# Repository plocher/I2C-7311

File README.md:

# I2C-7311
## License: CERN Open Hardware Licence v1.2

IO Expander with 4x IO4 connections

### Introduction

This board was originally produced to help me build control panels for
my model railroad - I needed to connect many different buttons, switches
and lights to an Arduino, and also connect the Arduino to a
communications bus (Ethernet, CAN or Loconet), and I couldn\'t find
anything that had both high IO point density AND visual feedback.

I started with a simple I2C based 32-pin Arduino
[IOShield](/pages/IOShield "wikilink") with monitoring LEDs on each pin
(Active-LOW inputs, LED is on when pin is grounded, writing a \"1\" to
the port pulls it to ground). I was aiming to support up to the max I2C
devices that can be used together, with the 8-bit board
[I2C-8574-IO](/pages/I2C-8574-IO "wikilink") (deprecated), that was a total of
8x boards with 128 i/o points.

The 7311 IO expanders used here will support up to 64 boards, with 1024
potential I/O points.

This latest design moves from overly generic and/or overly specialized
designs to a generic design with daughterboards that encapsulate the
appliance-specific buffering and logic. The benefits provided by these
IOB boards include:

-   Improved I/O bank utilization (leftover capacity is now a multiple
    of 4-bit daughtercard instead of 16-bit I2C card\...)
-   Riser height eliminates having to custom cut 3M track
-   Allows deprecation of cabling intensive signal driver IO4 and I2C
    boards
-   Allows custom circuitry to be added to Signal, Detector and Turtle
    drivers

### Cautions

With several hundred IO loads, and up to 256 external breakout devices,
a suitable power supply (or supplies) must be used.

In practice, a 3A 9-12VDC supply a good choice for most small to medium
sized control points.

This supply needs to power the core processor, its direct IO loads, the
I2C expander chain AND provide \~100mA to each IO4 device. Instead of
relying on the Arduino\'s onboard regulated supply (which is only good
for about 100mA itself), each board has its own regulator with a common
supply feed that can handle up to 4A @ 12v. If more power is needed, the
daisy chained power feed thru can be replaced with a per-board
independent supply.

### Specifications

This IO board is based on the MAX7311/12 16 bit IO Expander, with a a
bank of 4x I/O Boards. These IOBs contain buffered LED drivers connected
to LEDs that show the status of the I/O lines in real time. They also
contain the needed circuitry to drive / sense the appliances connected
to them. See

-   [IOB-Inputs](/pages/IOB-Inputs "wikilink") 4x buffered inputs
-   [IOB-Outputs](/pages/IOB-Outputs "wikilink") 4x buffered outputs
-   [IOB-Turtle](/pages/IOB-Turtle "wikilink") 1x buffered output and 3x buffered inputs
-   [IOB-Signal](/pages/IOB-Signal "wikilink") 2x RGB signal head driver (Dark, Stop, Approach, Clear)

Each board provides a latched set of 16x IO points, with each point
being software selectable to be either an input or an output. The
individual points are reasonably protected from the environment, and can
sink 10 mA each (with the MAX7312, they can also drive \~20mA). By using
active low inputs and outputs, the effects of environmental noise are
reduced - remote sensors only need to ground an I/O point to register
activity.

#### Communication Protocol {#communication_protocol}

```C++
Simple I2C 16-bit Reads and Writes:
uint16_t I2Cexpander::read7311() {
    uint16_t data = 0;
    Wire.beginTransmission(_i2c_address);
    Wire.write(REGISTER_7311INPUT);
    Wire.endTransmission();
    // Wire.beginTransmission(_i2c_address);
    Wire.requestFrom(_i2c_address, (uint8_t)2);
    if(Wire.available()) {
        data = Wire.read();
    }
    if(Wire.available()) {
        data |= (Wire.read() << 8);
    }
    // Wire.endTransmission();
    return data;
}

void I2Cexpander::write7311(uint16_t data) {
    data = data | _config;
    Wire.beginTransmission(_i2c_address);
    Wire.write(REGISTER_7311OUTPUT);
    Wire.write(0xff & data);  //  low byte
    Wire.write(data >> 8);    //  high byte
    Wire.endTransmission();
}
```

See [I2Cexpander-lib](/pages/I2Cexpander "wikilink") for a more complete interface
library.

#### Addressing

**AD2**|**AD1**|**AD0**|**A6**|**A5**|**A4**|**A3**|**A2**|**A1**|**A0**|**ADDRESS (HEX)**
:-----:|:-----:|:-----:|:-----:|:-----:|:-----:|:-----:|:-----:|:-----:|:-----:|:-----:
GND|SCL|GND|0|0|1|0|0|0|0|0x20
GND|SCL|V+|0|0|1|0|0|0|1|0x22
GND|SDA|GND|0|0|1|0|0|1|0|0x24
GND|SDA|V+|0|0|1|0|0|1|1|0x26
V+|SCL|GND|0|0|1|0|1|0|0|0x28
V+|SCL|V+|0|0|1|0|1|0|1|0x2A
V+|SDA|GND|0|0|1|0|1|1|0|0x2C
V+|SDA|V+|0|0|1|0|1|1|1|0x2E
GND|SCL|SCL|0|0|1|1|0|0|0|0x30
GND|SCL|SDA|0|0|1|1|0|0|1|0x32
GND|SDA|SCL|0|0|1|1|0|1|0|0x34
GND|SDA|SDA|0|0|1|1|0|1|1|0x36
V+|SCL|SCL|0|0|1|1|1|0|0|0x38
V+|SCL|SDA|0|0|1|1|1|0|1|0x3A
V+|SDA|SCL|0|0|1|1|1|1|0|0x3C
V+|SDA|SDA|0|0|1|1|1|1|1|0x3E
GND|GND|GND|0|1|0|0|0|0|0|0x40
GND|GND|V+|0|1|0|0|0|0|1|0x42
GND|V+|GND|0|1|0|0|0|1|0|0x44
GND|V+|V+|0|1|0|0|0|1|1|0x46
V+|GND|GND|0|1|0|0|1|0|0|0x48
V+|GND|V+|0|1|0|0|1|0|1|0x4A
V+|V+|GND|0|1|0|0|1|1|0|0x4C
V+|V+|V+|0|1|0|0|1|1|1|0x4E
GND|GND|SCL|0|1|0|1|0|0|0|0x50
GND|GND|SDA|0|1|0|1|0|0|1|0x52
GND|V+|SCL|0|1|0|1|0|1|0|0x54
GND|V+|SDA|0|1|0|1|0|1|1|0x56
V+|GND|SCL|0|1|0|1|1|0|0|0x58
V+|GND|SDA|0|1|0|1|1|0|1|0x5A
V+|V+|SCL|0|1|0|1|1|1|0|0x5C
V+|V+|SDA|0|1|0|1|1|1|1|0x5E
SCL|SCL|GND|1|0|1|0|0|0|0|0xA0
SCL|SCL|V+|1|0|1|0|0|0|1|0xA2
SCL|SDA|GND|1|0|1|0|0|1|0|0xA4
SCL|SDA|V+|1|0|1|0|0|1|1|0xA6
SDA|SCL|GND|1|0|1|0|1|0|0|0xA8
SDA|SCL|V+|1|0|1|0|1|0|1|0xAA
SDA|SDA|GND|1|0|1|0|1|1|0|0xAC
SDA|SDA|V+|1|0|1|0|1|1|1|0xAE
SCL|SCL|SCL|1|0|1|1|0|0|0|0xB0
SCL|SCL|SDA|1|0|1|1|0|0|1|0xB2
SCL|SDA|SCL|1|0|1|1|0|1|0|0xB4
SCL|SDA|SDA|1|0|1|1|0|1|1|0xB6
SDA|SCL|SCL|1|0|1|1|1|0|0|0xB8
SDA|SCL|SDA|1|0|1|1|1|0|1|0xBA
SDA|SDA|SCL|1|0|1|1|1|1|0|0xBC
SDA|SDA|SDA|1|0|1|1|1|1|1|0xBE
SCL|GND|GND|1|1|0|0|0|0|0|0xC0
SCL|GND|V+|1|1|0|0|0|0|1|0xC2
SCL|V+|GND|1|1|0|0|0|1|0|0xC4
SCL|V+|V+|1|1|0|0|0|1|1|0xC6
SDA|GND|GND|1|1|0|0|1|0|0|0xC8
SDA|GND|V+|1|1|0|0|1|0|1|0xCA
SDA|V+|GND|1|1|0|0|1|1|0|0xCC
SDA|V+|V+|1|1|0|0|1|1|1|0xCE
SCL|GND|SCL|1|1|0|1|0|0|0|0xD0
SCL|GND|SDA|1|1|0|1|0|0|1|0xD2
SCL|V+|SCL|1|1|0|1|0|1|0|0xD4
SCL|V+|SDA|1|1|0|1|0|1|1|0xD6
SDA|GND|SCL|1|1|0|1|1|0|0|0xD8
SDA|GND|SDA|1|1|0|1|1|0|1|0xDA
SDA|V+|SCL|1|1|0|1|1|1|0|0xDC
SDA|V+|SDA|1|1|0|1|1|1|1|0xDE

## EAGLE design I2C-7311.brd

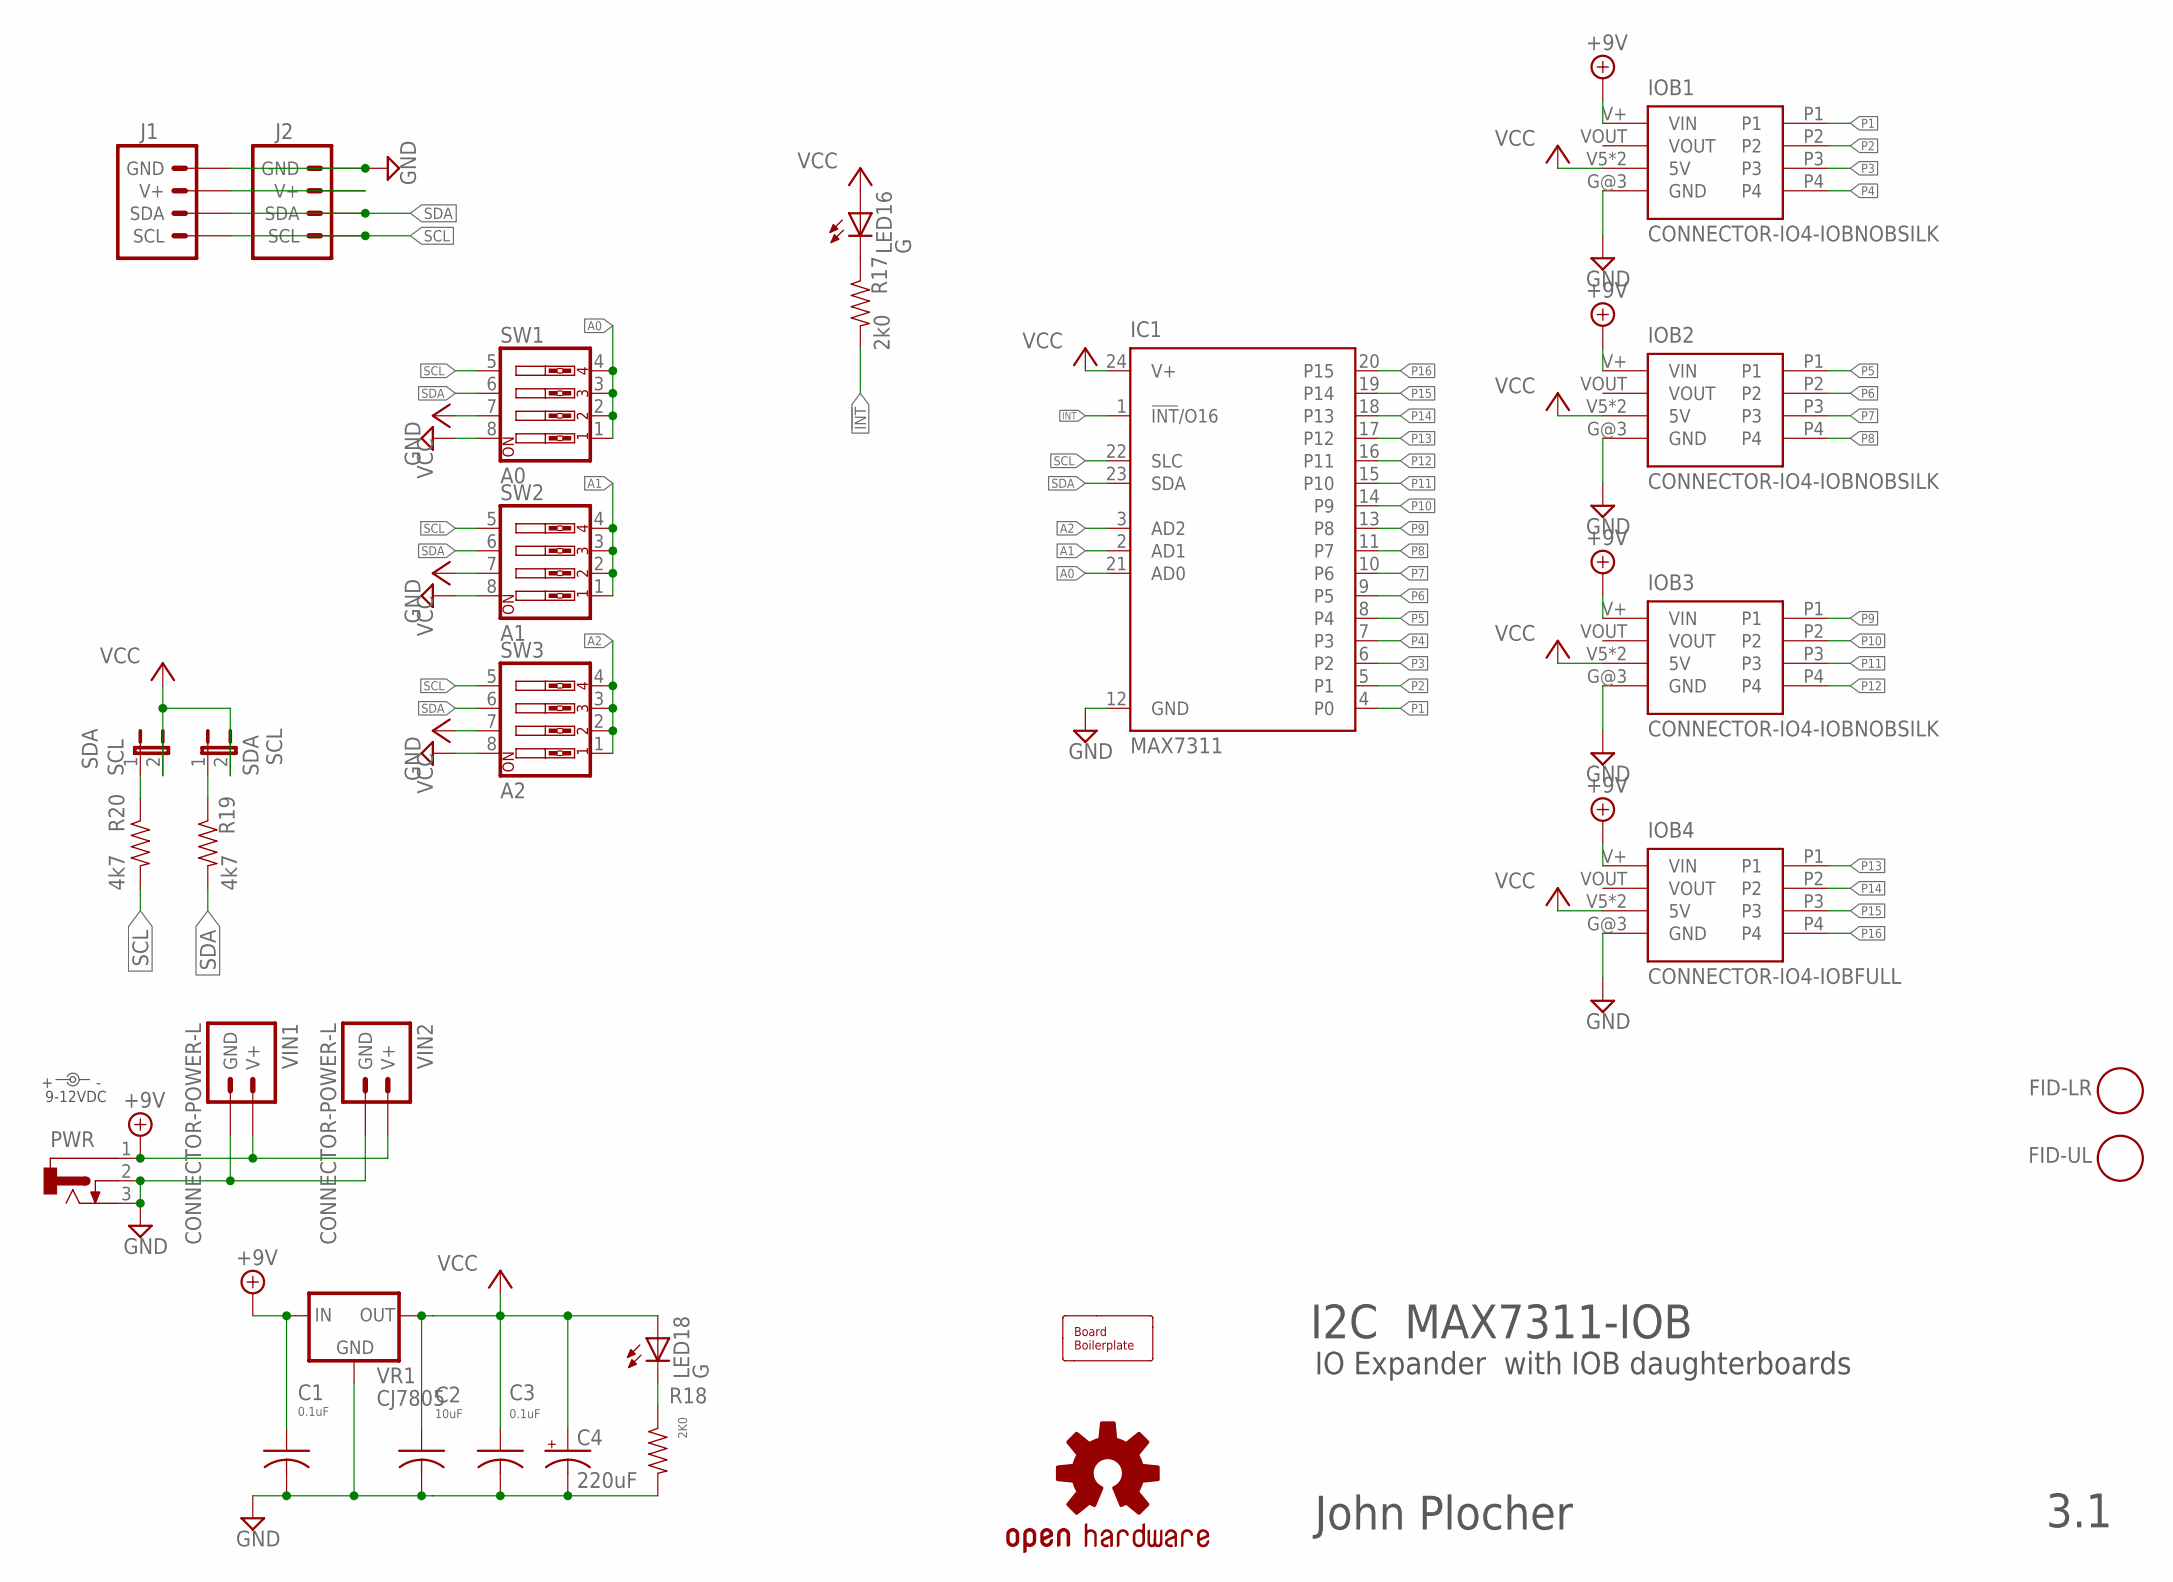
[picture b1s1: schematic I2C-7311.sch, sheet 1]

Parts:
BOARD1: BOARD80X100-IOB; BOARD-DINRAIL-3.17IN-IOB
C1, C3: 0.1uF; 0805-CAP
C2: 10uF; 0805-CAP
C4: 220uF; 0810-CAP
FID-LR: FIDUCIAL; FIDUCIAL_1MM
FID-UL: FIDUCIAL; FIDUCIAL_1MM
IC1: MAX7311; TSSOP24
IOB1, IOB2, IOB3: CONNECTOR-IO4-IOBNOBSILK; IOB-IO4-NOBOTSILK
IOB4: CONNECTOR-IO4-IOBFULL; IO4-IOB
J1, J2: CONNECTOR-I2CLEFT; I2C-L
LED16, LED18: G; 0603-LED
PWR: CONNECTOR-DC-POWER-RA; DCJ0202
R17: 2k0; 0805-RES
R18: 2K0; 0805-RES
R19, R20: 4k7; 0805-RES
SCL: SDA; 1X02_LOCK
SDA: SCL; 1X02_LOCK
SW1: A0; EDG-04
SW2: A1; EDG-04
SW3: A2; EDG-04
U$1: OSHW-LOGOL; OSHW-LOGO-L
VIN: 9-12VDC; PWR_LABEL
VIN1, VIN2: CONNECTOR-POWER-L; POWER-R2
VR1: CJ7805; TO-252

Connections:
!INT: IC1.1 (!INT!/O16), R17.2
+9V: C1.1, IOB1.V+ (VIN), IOB2.V+ (VIN), IOB3.V+ (VIN), IOB4.V+ (VIN), PWR.1, VIN1.V+, VIN1.V+@1 (V+), VIN1.V+@2 (V+), VIN1.V+@3 (V+), VIN2.V+, VIN2.V+@1 (V+), VIN2.V+@2 (V+), VIN2.V+@3 (V+), VR1.1 (IN)
A0: IC1.21 (AD0), SW1.1, SW1.2, SW1.3, SW1.4
A1: IC1.2 (AD1), SW2.1, SW2.2, SW2.3, SW2.4
A2: IC1.3 (AD2), SW3.1, SW3.2, SW3.3, SW3.4
GND: C1.2, C2.2, C3.2, C4.-, IC1.12 (GND), IOB1.G@3 (GND), IOB2.G@3 (GND), IOB3.G@3 (GND), IOB4.G@3 (GND), J1.GND, J1.GND@1 (GND), J2.GND, J2.GND@1 (GND), PWR.2, PWR.3, R18.2, SW1.8, SW2.8, SW3.8, VIN1.GND, VIN1.GND@1 (GND), VIN1.GND@2 (GND), VIN1.GND@3 (GND), VIN2.GND, VIN2.GND@1 (GND), VIN2.GND@2 (GND), VIN2.GND@3 (GND), VR1.2 (GND); also elsewhere on the board
unnamed: LED18.C, R18.1
unnamed: R19.1, SCL.1
unnamed: R20.1, SDA.1
unnamed: LED16.C, R17.1
P1: IC1.4 (P0), IOB1.P1; also elsewhere on the board
P2: IC1.5 (P1), IOB1.P2; also elsewhere on the board
P3: IC1.6 (P2), IOB1.P3; also elsewhere on the board
P4: IC1.7 (P3), IOB1.P4; also elsewhere on the board
P5: IC1.8 (P4), IOB2.P1; also elsewhere on the board
P6: IC1.9 (P5), IOB2.P2; also elsewhere on the board
P7: IC1.10 (P6), IOB2.P3; also elsewhere on the board
P8: IC1.11 (P7), IOB2.P4; also elsewhere on the board
P9: IC1.13 (P8), IOB3.P1; also elsewhere on the board
P10: IC1.14 (P9), IOB3.P2; also elsewhere on the board
P11: IC1.15 (P10), IOB3.P3; also elsewhere on the board
P12: IC1.16 (P11), IOB3.P4; also elsewhere on the board
P13: IC1.17 (P12), IOB4.P1; also elsewhere on the board
P14: IC1.18 (P13), IOB4.P2; also elsewhere on the board
P15: IC1.19 (P14), IOB4.P3; also elsewhere on the board
P16: IC1.20 (P15), IOB4.P4; also elsewhere on the board
SCL: IC1.22 (SLC), J1.SCL, J1.SCL@1 (SCL), J2.SCL, J2.SCL@1 (SCL), R20.2, SW1.5, SW2.5, SW3.5
SDA: IC1.23 (SDA), J1.SDA, J1.SDA@1 (SDA), J2.SDA, J2.SDA@1 (SDA), R19.2, SW1.6, SW2.6, SW3.6
V+I2C: J1.V+, J1.V+@1 (V+), J2.V+, J2.V+@1 (V+)
VCC: C2.1, C3.1, C4.+, IC1.24 (V+), IOB1.V5 (5V), IOB1.V5@1 (5V), IOB2.V5 (5V), IOB2.V5@1 (5V), IOB3.V5 (5V), IOB3.V5@1 (5V), IOB4.V5 (5V), IOB4.V5@1 (5V), LED16.A, LED18.A, SCL.2, SDA.2, SW1.7, SW2.7, SW3.7, VR1.3 (OUT); also elsewhere on the board

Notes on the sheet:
I2C MAX7311-IOB
IO Expander with IOB daughterboards
John Plocher
3.1

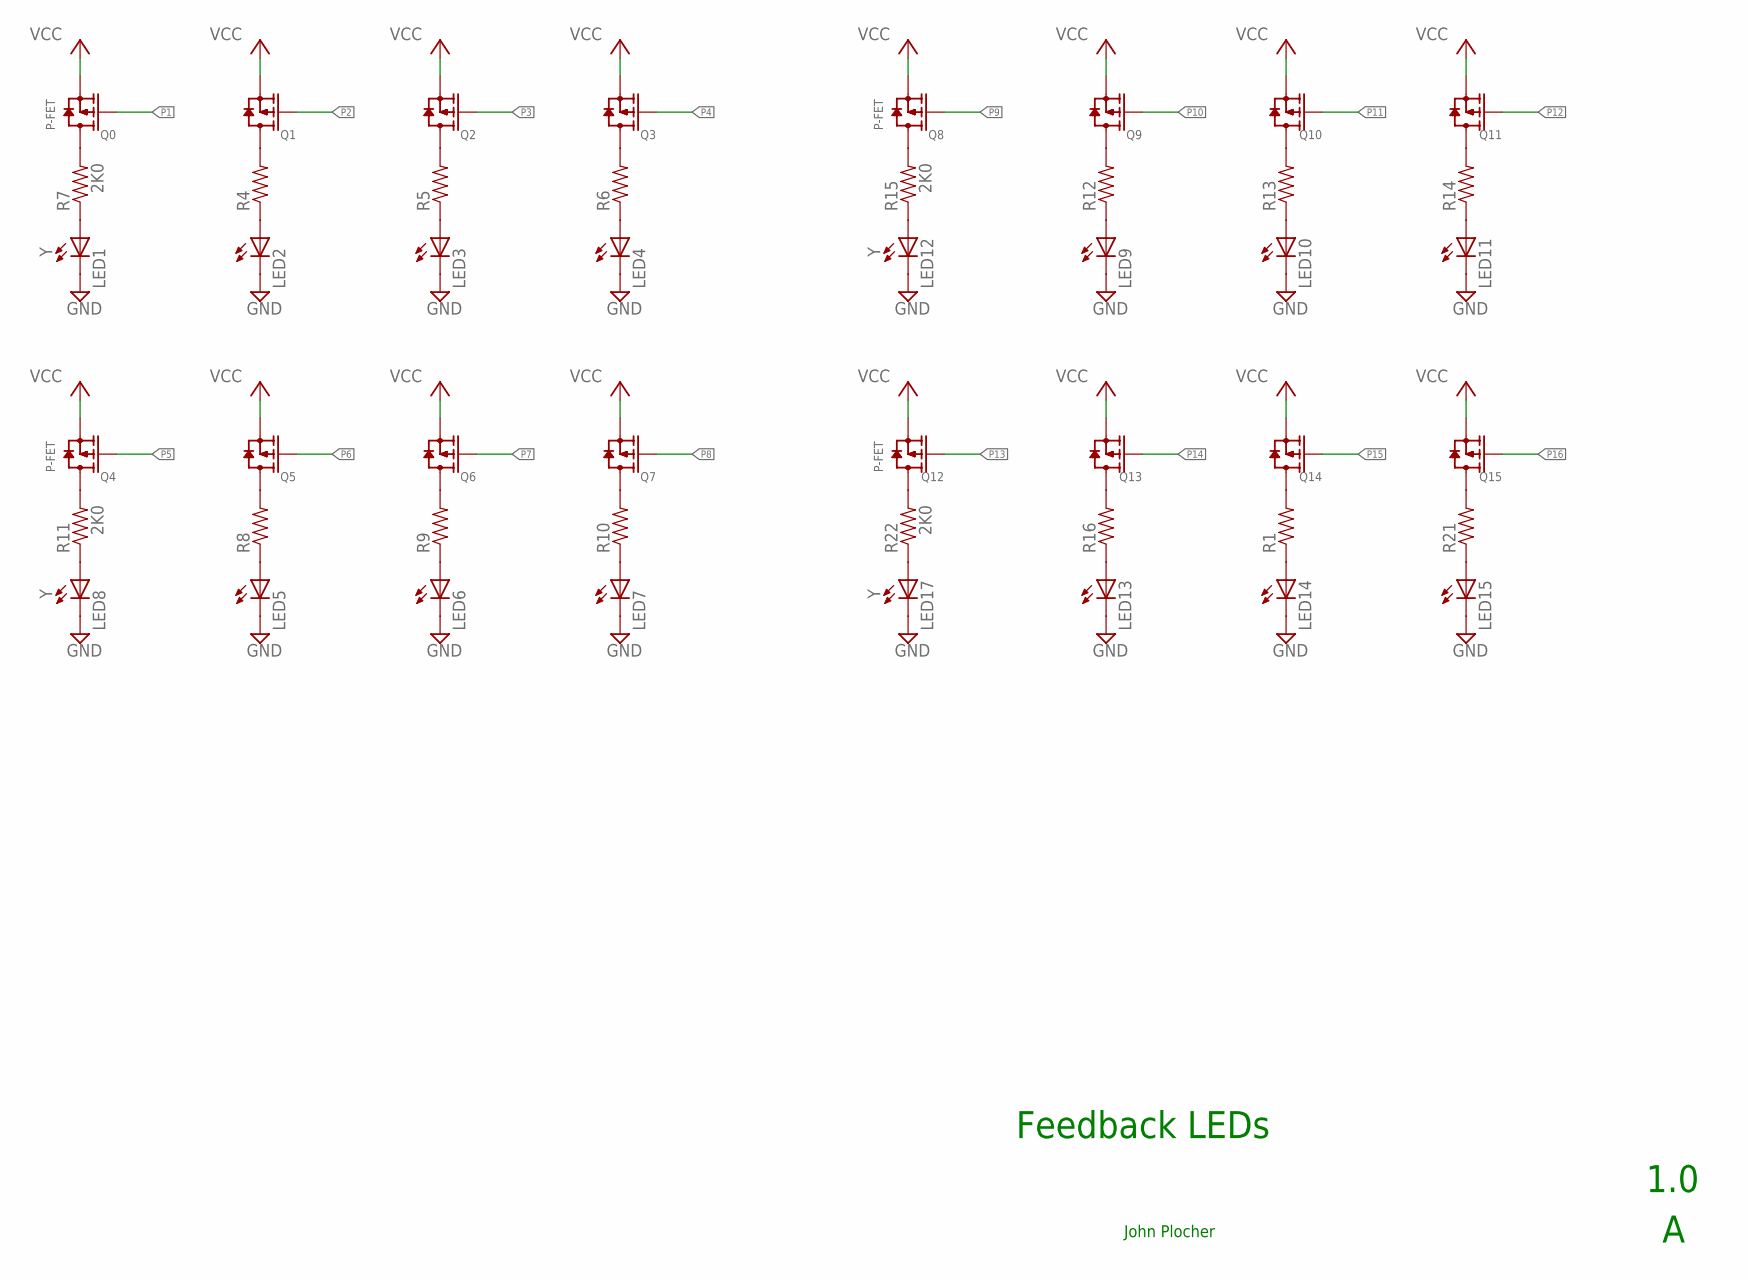
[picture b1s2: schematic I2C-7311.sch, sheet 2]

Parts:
LED1, LED2, LED3, LED4, LED5, LED6, LED7, LED8, LED9, LED10, LED11, LED12, LED13, LED14, LED15, LED17: Y; 0603-LED
Q0, Q1, Q2, Q3, Q4, Q5, Q6, Q7, Q8, Q9, Q10, Q11, Q12, Q13, Q14, Q15: P-FET; SOT23
R1, R4, R5, R6, R7, R8, R9, R10, R11, R12, R13, R14, R15, R16, R21, R22: 2K0; 0805-RES

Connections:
GND: LED1.C, LED2.C, LED3.C, LED4.C, LED5.C, LED6.C, LED7.C, LED8.C, LED9.C, LED10.C, LED11.C, LED12.C, LED13.C, LED14.C, LED15.C, LED17.C; also elsewhere on the board
unnamed: Q4.3 (D), R11.2
unnamed: Q5.3 (D), R8.2
unnamed: Q6.3 (D), R9.2
unnamed: Q7.3 (D), R10.2
unnamed: LED8.A, R11.1
unnamed: LED5.A, R8.1
unnamed: LED6.A, R9.1
unnamed: LED7.A, R10.1
unnamed: Q8.3 (D), R15.2
unnamed: Q9.3 (D), R12.2
unnamed: Q10.3 (D), R13.2
unnamed: Q11.3 (D), R14.2
unnamed: LED12.A, R15.1
unnamed: LED9.A, R12.1
unnamed: LED10.A, R13.1
unnamed: LED11.A, R14.1
unnamed: Q12.3 (D), R22.2
unnamed: Q13.3 (D), R16.2
unnamed: Q14.3 (D), R1.2
unnamed: Q15.3 (D), R21.2
unnamed: LED17.A, R22.1
unnamed: LED13.A, R16.1
unnamed: LED14.A, R1.1
unnamed: LED15.A, R21.1
unnamed: Q0.3 (D), R7.2
unnamed: Q1.3 (D), R4.2
unnamed: Q2.3 (D), R5.2
unnamed: Q3.3 (D), R6.2
unnamed: LED1.A, R7.1
unnamed: LED2.A, R4.1
unnamed: LED3.A, R5.1
unnamed: LED4.A, R6.1
P1: Q0.1 (G); also elsewhere on the board
P2: Q1.1 (G); also elsewhere on the board
P3: Q2.1 (G); also elsewhere on the board
P4: Q3.1 (G); also elsewhere on the board
P5: Q4.1 (G); also elsewhere on the board
P6: Q5.1 (G); also elsewhere on the board
P7: Q6.1 (G); also elsewhere on the board
P8: Q7.1 (G); also elsewhere on the board
P9: Q8.1 (G); also elsewhere on the board
P10: Q9.1 (G); also elsewhere on the board
P11: Q10.1 (G); also elsewhere on the board
P12: Q11.1 (G); also elsewhere on the board
P13: Q12.1 (G); also elsewhere on the board
P14: Q13.1 (G); also elsewhere on the board
P15: Q14.1 (G); also elsewhere on the board
P16: Q15.1 (G); also elsewhere on the board
VCC: Q0.2 (S), Q1.2 (S), Q2.2 (S), Q3.2 (S), Q4.2 (S), Q5.2 (S), Q6.2 (S), Q7.2 (S), Q8.2 (S), Q9.2 (S), Q10.2 (S), Q11.2 (S), Q12.2 (S), Q13.2 (S), Q14.2 (S), Q15.2 (S); also elsewhere on the board

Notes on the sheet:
Feedback LEDs
1.0
John Plocher

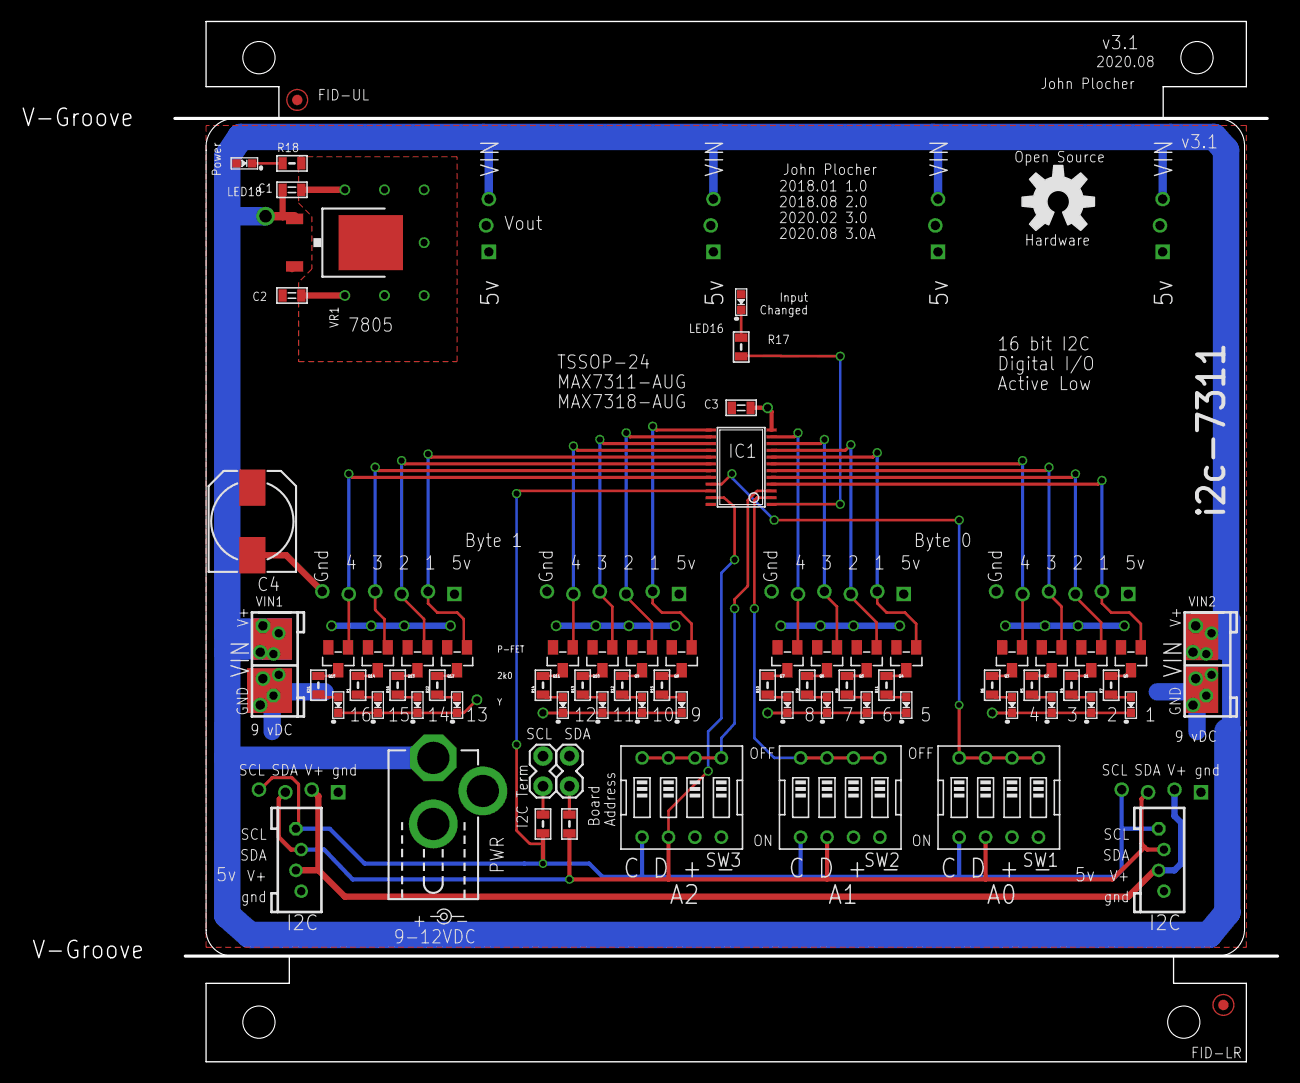
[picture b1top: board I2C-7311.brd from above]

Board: 2 copper layers, 120.7 x 99.8 mm, 79 parts (0 on the bottom side), 62 nets.

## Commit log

2019-12-07 Added graphic
2020-03-07 3.0 - new IOB design
2020-04-19 updated SPCoast lib for IO4-IOB silkscreen
2020-05-04 updated tags
2020-08-05 updated SPCoast.lbr: LED, VR, C-POL to match reel orientation
2020-08-05 V3.1
2020-08-05 V3.1 again
2020-08-12 SPCoast lbr footprint update
2020-09-11 fix markdown
